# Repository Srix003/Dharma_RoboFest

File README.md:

# DHARMA BOT :dog2::robot:

Dharma Bot is a sophisticated quadruped robotic dog featuring 12 degrees of freedom (DOF) for dynamic motion. The system includes a custom-designed remote control and smartwatch, which collectively offer seamless user interaction, control, and monitoring capabilities.

## Authors :writing_hand:

- [@mr-spaw](https://github.com/mr-spaw) :space_invader:
- [@LordCretivo](https://github.com/LordCretivo) :teddy_bear:
- [@DeepseaBandit](https://github.com/DeepseaBandit) :merman:

## Documentation :notebook_with_decorative_cover:

[Documentation](https://docs.google.com/document/d/14A3U6bSW9qBQt6sxEBGoiQTC8-wSntHT5azrs7TC3jw/edit?usp=sharing)

## System Overview :joystick: 
Dharma Bot is composed of three primary, electronically independent subsystems:
1. **The Bot**: The robotic dog, with core control and motion capabilities.
2. **Smart Remote**: The main control interface for the bot, featuring a Raspberry Pi, touchscreen, and long-range communication.
3. **Smartwatch**: A peripheral control and monitoring device equipped with sensors and ESP-32-based communications.
4. **Turret System**: The turret system is a rotating module mounted on the bot, designed to carry cameras and sensors. It provides 360-degree horizontal rotation and adjustable vertical tilt, enabling the bot to monitor or track targets in multiple directions.

## Subsystems

### [Smart Watch](Firmware/Utility_Watch/watch.md) :watch:
The smartwatch incorporates:
- **ESP-32 WROOM microcontroller**:The SoC of the embedded hardware.
- **OLED screen**: Displays real-time status, bot location, connectivity, and enemy detection data.
- **Pulse-meter sensor** and **GPS**: For monitoring the wearer's health and position.
- **Geotagging**: Logs location of deployed tags for tracking.
- **Heartbeat Monitoring**: In "Military Mode," it locks if the wearer’s pulse reads zero for over 30 seconds.
- **FailSafe Mechanism**: Notifies the remote of the current location upon triggering specific emergency conditions.
- **ESP-NOW Communication**: Provides secure data exchange between the smartwatch and the smart remote.

### Smart Remote  :video_game:
Serving as the primary control hub, the smart remote includes:
- **Raspberry Pi and 7-inch HDMI Touchscreen**: For intuitive control of the whole system architecture.
- **LoRa and ESP-NOW Modules**: Enabling long-range communication up to 10 km in LoRA and about five meters of communication with ESP-NOW protocol
- **GeoTag Integration**: Displays tagged locations on a map for rescue and tracking.
- **Video Streaming**: ESP-32 S3 CAM streaming for real-time surveillance.
- **Manual Controls**: Joysticks, potentiometers, and switches for bot locomotion and firing systems.
- **GUI**: The remote’s GUI interface provides a user-friendly experience, offering control over various modes, video feeds, and sensor data

### PoC Bot :dog2:
The main bot integrates:
- **Teensy 4.1 Microcontroller**: Manages core functions, including servo control and scheduling of Tasks
- **ESP 32 S3 Development Board**: Controlling the Peripheral Electronics like GPS, ToF Sensors and Gyroscopic Readngs.
- **MG99R Servo Motors**: 12 servo motors for precise locomotion.
- **ESP-32 S3 Camera System**: A esp camera system for live video feed.
- **LIDAR and GPS Modules**: For navigation and environmental awareness.
- **Communication**:  Local esp aceess network and long-range LoRa for data exchange between subsystems.

### Turret System :gun:
The turrent has:
- **Raspberry Pi**: Runs a local ML image recognition model and manages peripheral hardware.
- **ESP 32**: Controls the Servo motors

## Installation-Arduino IDE :computer:

### Ubuntu-linux64

Update Packages

```bash
sudo apt update
sudo apt upgrade
```

Installing Dependencies
```bash
sudo apt install -y wget unzip
```

Download the Arduino IDE
```bash
wget https://downloads.arduino.cc/arduino-<version>-linux64.tar.xz
```

Extract the Archive
```bash
tar -xf arduino-<version>-linux64.tar.xz
```

Install the Arduino IDE
```bash
cd arduino-<version>
sudo ./install.sh
```

Download the Arduino IDE
```bash
sudo usermod -aG dialout $USER
```

Launch Arduino IDE from Application menu or
[Arduino](https://www.arduino.cc/en/software)

then,
Go to File > Preferences (or Arduino > Preferences on macOS).
In the Preferences window, look for the field labeled Additional Board Manager URLs.
Paste the URLs for any additional board packages

```bash
http://arduino.esp8266.com/stable/package_esp8266com_index.json
https://github.com/earlephilhower/arduino-pico/releases/download/global/package_rp2040_index.json
https://raw.githubusercontent.com/espressif/arduino-esp32/gh-pages/package_esp32_index.json
https://www.pjrc.com/teensy/package_teensy_index.json
```
Go to Tools > Board > Board Manager.
Download ESP and Raspberry Pi Pico Board libraries
## 

## Project Context :star: :india:
This project was developed as part of RoboFest, held in 2024, organised by Gujarat Council on Science and Technology(GUJCOST).

## Social Media :star2:
[Website](https://krs.kiit.ac.in)
[Instagram](https://www.instagram.com/kiit_robotics.society?utm_source=ig_web_button_share_sheet&igsh=ZDNlZDc0MzIxNw==)
[Linkedin](https://www.linkedin.com/company/kiit-robotics-society-bbsr/mycompany/)

## Project Link :link:
https://github.com/mr-spaw/Dharma_RoboFest

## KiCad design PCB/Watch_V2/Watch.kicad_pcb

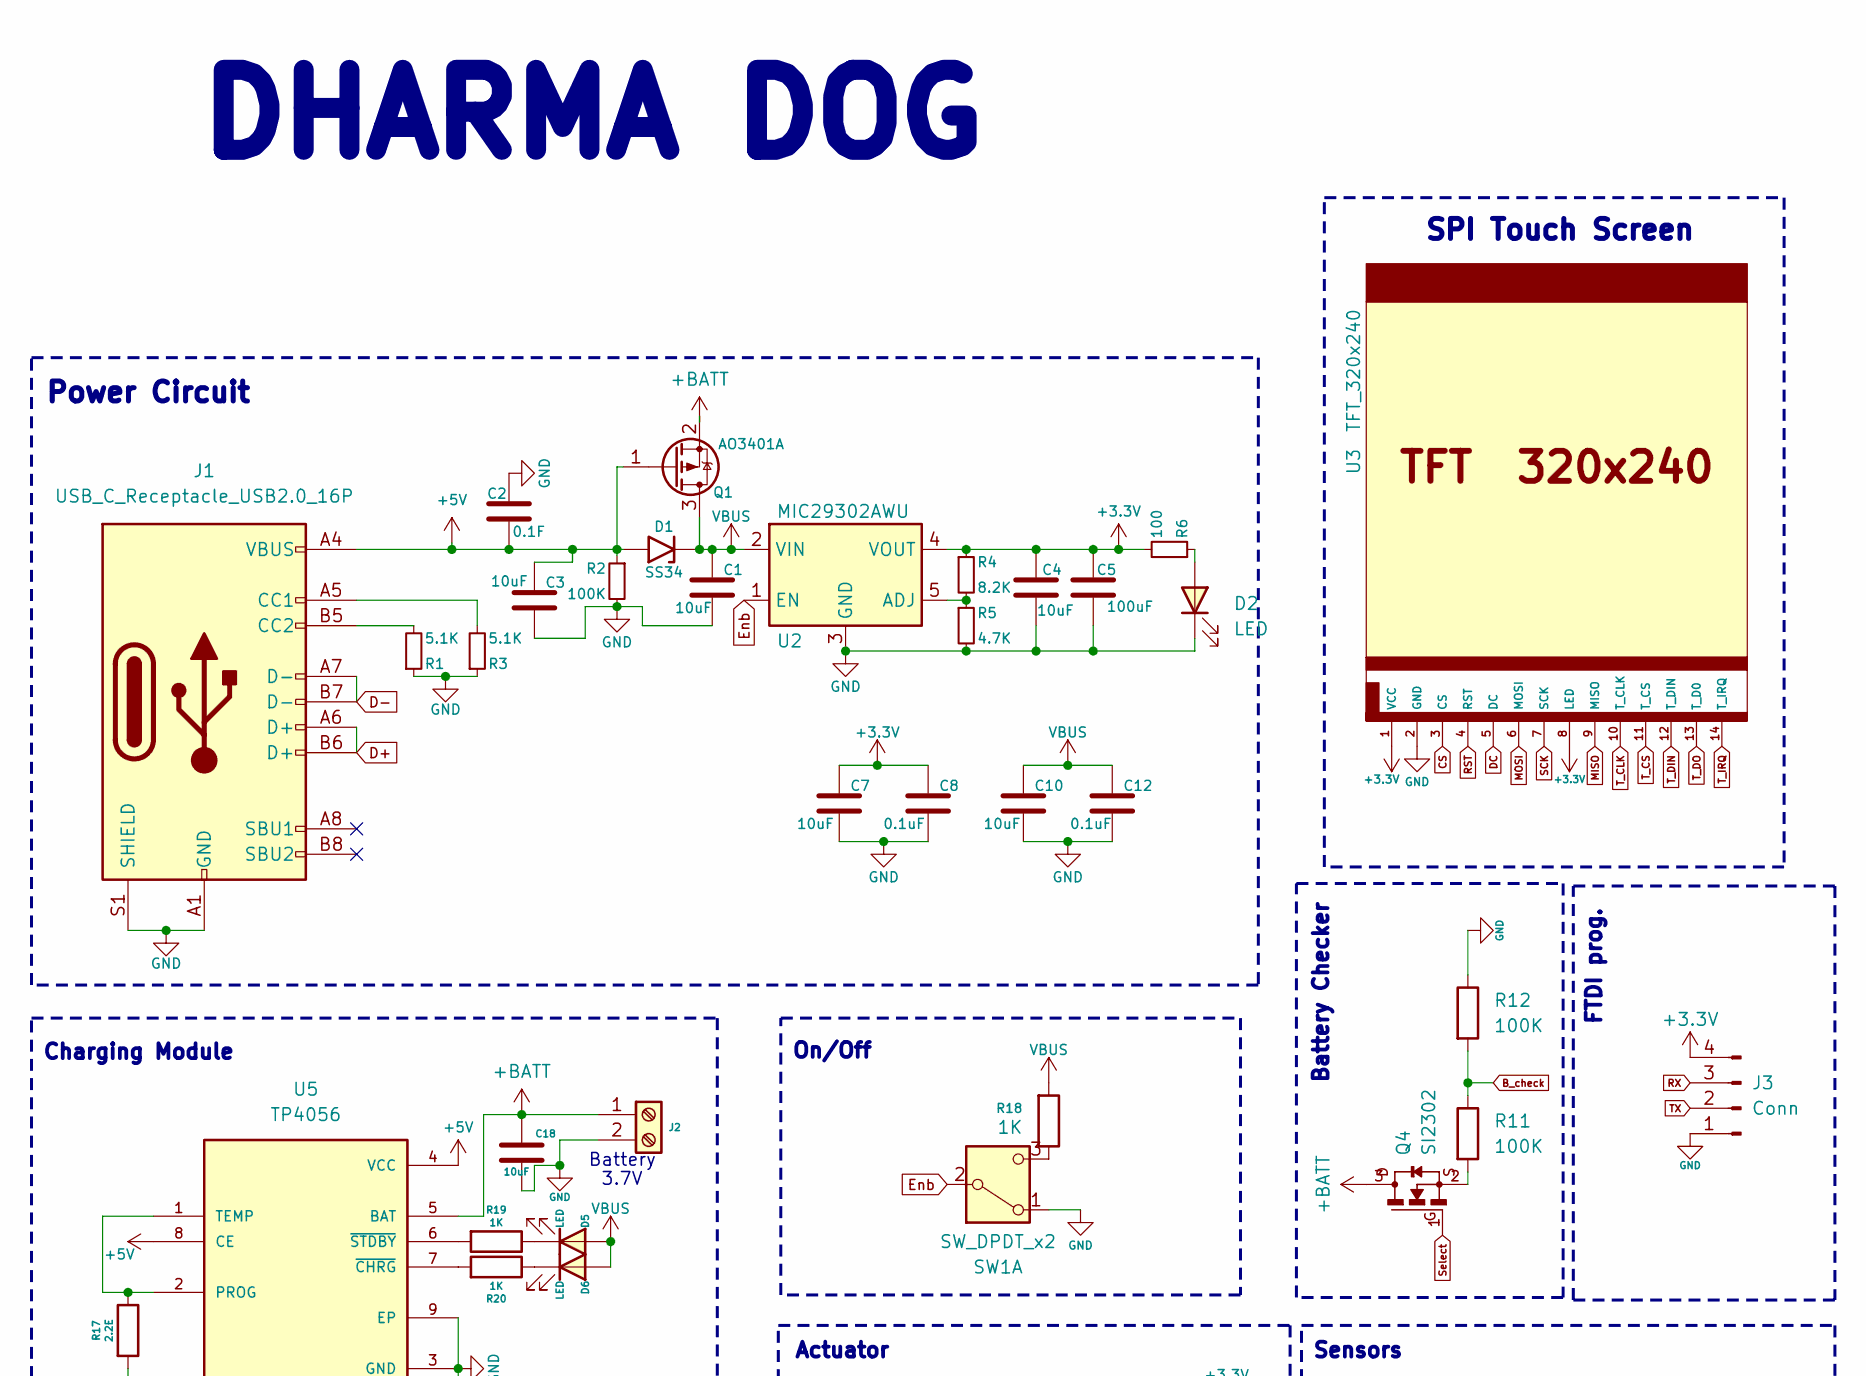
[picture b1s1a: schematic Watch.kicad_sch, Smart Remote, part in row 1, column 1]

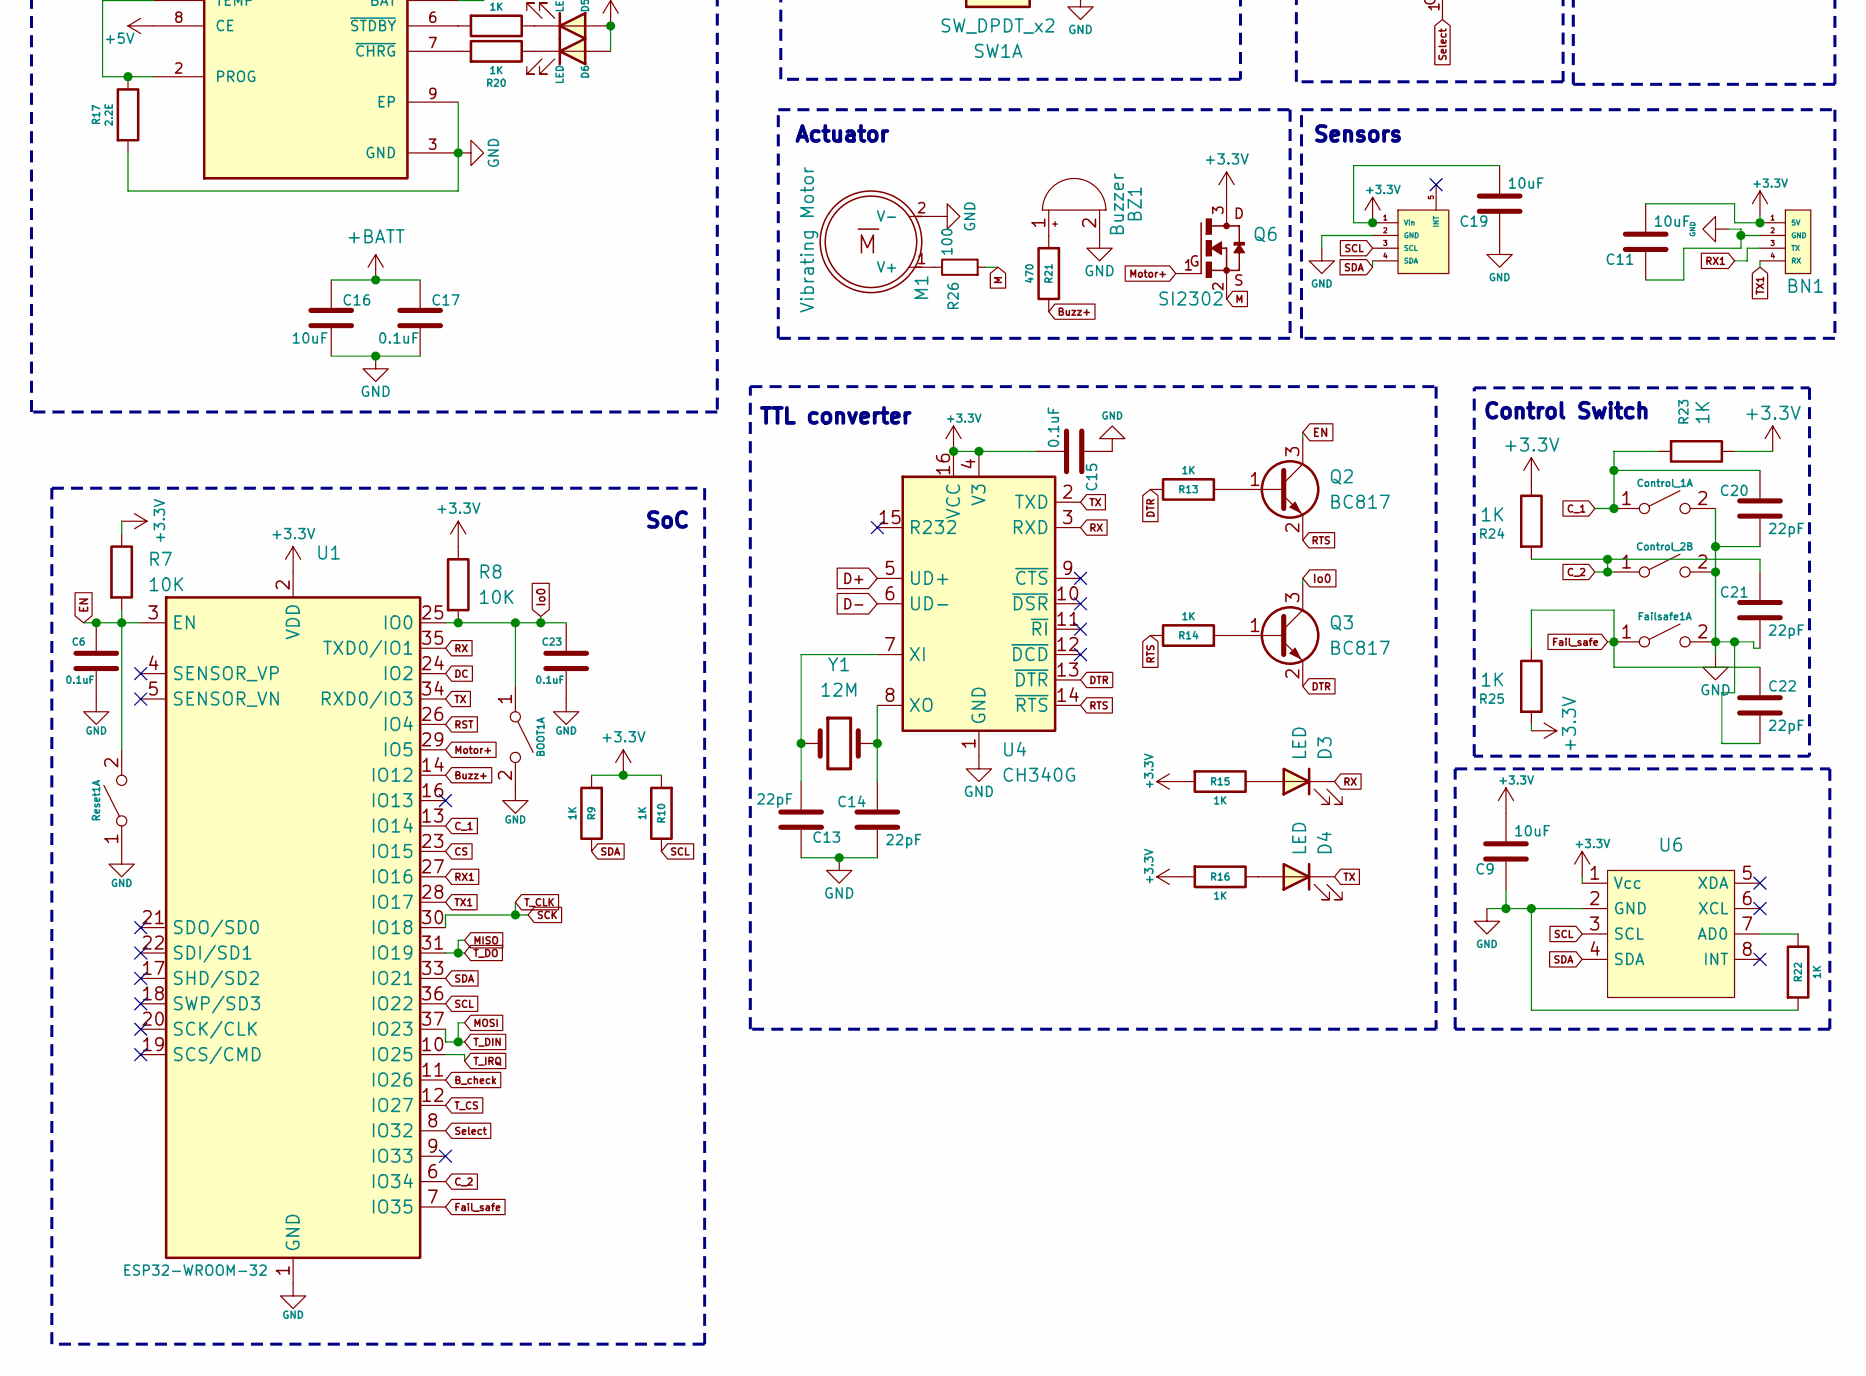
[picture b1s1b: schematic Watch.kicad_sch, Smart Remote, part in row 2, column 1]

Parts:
BN1: gps footprinbt
BOOT1: SW_DPST_x2; SW_PUSH_6mm_H5mm
BZ1: Buzzer; Buzzer_12x9.5RM7.6
C1, C3, C4, C7, C9, C10, C11, C16, C18, C19: 10uF; C_1206_3216Metric
C2: 0.1F; C_1206_3216Metric
C5: 100uF; C_1206_3216Metric
C6, C8, C12, C15, C17, C23: 0.1uF; C_1206_3216Metric
C13, C14, C20, C21, C22: 22pF; C_1206_3216Metric
Control_1, Control_2: SW_DPST_x2; SW_PUSH_6mm_H5mm
D1: SS34; D_SMA
D2, D3, D4, D5, D6: LED; LED_1210_3225Metric
Failsafe1: SW_DPST_x2; SW_PUSH_6mm_H5mm
J1: USB_C_Receptacle_USB2.0_16P; USB_C_Receptacle_HCTL_HC-TYPE-C-16P-01A
J2: Screw_Terminal_01x02; Motor Vib
J3: Conn; PinHeader_1x04_P2.54mm_Vertical
M1: Vibrating Motor; Motor Vib
MAX1: module_max30102
Q1: AO3401A; SOT-23
Q2, Q3: BC817; SOT-23
Q4, Q6: SI2302; SOT23
R1, R3: 5.1K; R_0805_2012Metric
R2, R11, R12: 100K; R_0805_2012Metric
R4: 8.2K; R_0805_2012Metric
R5: 4.7K; R_0805_2012Metric
R6, R26: 100; R_0805_2012Metric
R7, R8: 10K; R_0805_2012Metric
R9, R10, R13, R14, R15, R16, R18, R19, R20, R22, R23, R24, R25: 1K; R_0805_2012Metric
R17: 2.2E; R_0805_2012Metric
R21: 470; R_0805_2012Metric
Reset1: SW_DPST_x2; SW_PUSH_6mm_H5mm
SW1: SW_DPDT_x2; SW_MINI-SPDT-SW
U1: ESP32-WROOM-32
U2: MIC29302AWU; TO-263-5_TabPin3
U3: TFT_320x240; TFT-320x240
U4: CH340G; SOIC-16_3.9x9.9mm_P1.27mm
U5: TP4056; SOP127P600X175-9N
U6: module_mpu6050
Y1: 12M; Crystal_HC49-4H_Vertical

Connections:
+3.3V: BN1.1 (5V), C4.1, C5.1, C7.1, C8.1, C9.2, C11.2, C15.2, C19.2, J3.4 (GND), MAX1.1 (Vin), Q6.3, R4.1, R6.2, R7.1, R8.1, R9.2, R10.2, R15.2, R16.2, R23.1, R24.1, R25.2, U1.2 (VDD), U2.4 (VOUT), U3.1 (VCC), U3.8 (LED), U4.4 (V3), U4.16 (VCC), U6.1 (Vcc)
+5V: C2.2, C3.1, D1.2 (A2), J1.A4 (VBUS), J1.A9 (VBUS), J1.B4 (VBUS), J1.B9 (VBUS), Q1.1 (G), R2.1, U5.4 (VCC), U5.8 (CE)
+BATT: C16.1, C17.1, C18.1, J2.1 (+), Q1.2 (S), Q4.3, U5.5 (BAT)
B_check: R11.1, R12.2, U1.11 (IO26)
Buzz+: R21.1, U1.14 (IO12)
CS: U1.23 (IO15), U3.3 (CS)
C_1: C20.1, Control_1.1 (A), R23.2, U1.13 (IO14)
C_2: C21.1, Control_2.1 (A), R24.2, U1.6 (IO34)
D+: J1.A6 (D+), J1.B6 (D+), U4.5 (UD+)
D-: J1.A7 (D-), J1.B7 (D-), U4.6 (UD-)
DC: U1.24 (IO2), U3.5 (DC)
DTR: Q3.2 (E), R13.1, U4.13 (~DTR)
EN: C6.2, Q2.3 (C), R7.2, Reset1.2 (B), U1.3 (EN)
Enb: SW1.2 (B), U2.1 (EN)
Fail_safe: C22.1, Failsafe1.1 (A), R25.1, U1.7 (IO35)
GND: BN1.2 (GND), BOOT1.2 (B), BZ1.2 (-), C1.2, C2.1, C3.2, C4.2, C5.2, C6.1, C7.2, C8.2, C9.1, C10.2, C11.1, C12.2, C13.1, C14.2, C15.1, C16.2, C17.2, C18.2, C19.1, C20.2, C21.2, C22.2, C23.1, Control_1.2 (B), Control_2.2 (B), D2.1 (K), Failsafe1.2 (B), J1.A1 (GND), J1.A12 (GND), J1.B1 (GND), J1.B12 (GND), J1.S1 (SHIELD), J2.2 (-), J3.1 (3.3), M1.2 (V-), MAX1.2 (GND), R1.1, R2.2, R3.1, R5.2, R12.1, R17.2, R22.2, Reset1.1 (A), SW1.1 (A), U1.1 (GND), U1.15 (GND), U1.38 (GND), U1.39 (GND), U2.3 (GND), U3.2 (GND), U4.1 (GND), U5.3 (GND), U5.9 (EP), U6.2 (GND)
Io0: BOOT1.1 (A), C23.2, Q3.3 (C), R8.2, U1.25 (IO0)
M: Q6.2, R26.1
MISO: U1.31 (IO19), U3.9 (MISO), U3.13 (T_D0)
MOSI: U1.37 (IO23), U3.6 (MOSI), U3.12 (T_DIN)
Motor+: Q6.1, U1.29 (IO5)
unnamed: BZ1.1 (+), R21.2
unnamed: D2.2 (A), R6.1
unnamed: D3.2 (A), R15.1
unnamed: D4.2 (A), R16.1
unnamed: D5.1 (K), R19.1
unnamed: D6.1 (K), R20.1
unnamed: J1.A5 (CC1), R3.2
unnamed: J1.B5 (CC2), R1.2
unnamed: M1.1 (V+), R26.2
unnamed: Q2.1 (B), R13.2
unnamed: Q3.1 (B), R14.2
unnamed: Q4.2, R11.2
unnamed: R18.1, SW1.3 (C)
unnamed: R4.2, R5.1, U2.5 (ADJ)
unnamed: C13.2, U4.7 (XI), Y1.1
unnamed: C14.1, U4.8 (XO), Y1.2
unnamed: R17.1, U5.1 (TEMP), U5.2 (PROG)
unnamed: R20.2, U5.7 (~CHRG)
unnamed: R19.2, U5.6 (~STDBY)
unnamed: R22.1, U6.7 (AD0)
RST: U1.26 (IO4), U3.4 (RST)
RTS: Q2.2 (E), R14.1, U4.14 (~RTS)
RX: D3.1 (K), J3.3 (TX), U1.35 (TXD0/IO1), U4.3 (RXD)
RX1: BN1.3 (TX), U1.27 (IO16)
SCK: U1.30 (IO18), U3.7 (SCK), U3.10 (T_CLK)
SCL: MAX1.3 (SCL), R10.1, U1.36 (IO22), U6.3 (SCL)
SDA: MAX1.4 (SDA), R9.1, U1.33 (IO21), U6.4 (SDA)
Select: Q4.1, U1.8 (IO32)
TX: D4.1 (K), J3.2 (RX), U1.34 (RXD0/IO3), U4.2 (TXD)
TX1: BN1.4 (RX), U1.28 (IO17)
T_CS: U1.12 (IO27), U3.11 (T_CS)
T_IRQ: U1.10 (IO25), U3.14 (T_IRQ)
VBUS: C1.1, C10.1, C12.1, D1.1 (A1), D5.2 (A), D6.2 (A), Q1.3 (D), R18.2, U2.2 (VIN)

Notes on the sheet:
Power Circuit
SPI Touch Screen
Sensors
FTDI prog.
SoC
Battery Checker
DHARMA DOG
Battery
TTL converter
Control Switch
3.7V
Charging Module
On/Off
Actuator

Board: 2 copper layers, 80 parts (0 on the bottom side), 54 nets, no tracks yet.

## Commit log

2024-11-10 added print function
2024-11-10 testing
2024-11-10 Updating Utility Watch
2024-11-10 adding remote
2024-11-10 adding remote and its communication
2024-11-10 adding PoC src
2024-11-10 datasheets
2024-11-10 raspi update
2024-11-10 adding datasheets
2024-11-10 updating BOM and pi_I2C
2024-11-10 Schematic Design
2024-11-10 adding BOM
2024-11-10 updated schematic V2
2024-11-10 updating Pcb-design
2024-11-10 updating picture
2024-11-10 Create Dharma_Bot.pdf
    updating documtation
2024-11-11 updating watch_v3 & remote_v2
2024-11-11 readme update
2024-11-11 update README file
2024-11-11 updating README
2024-11-11 updating icons and README
2024-11-11 updating README.md
2024-11-12 Update issue templates
2024-11-12 updating .github
2024-11-13 updating watch.md file
2024-11-15 Remote SRC
